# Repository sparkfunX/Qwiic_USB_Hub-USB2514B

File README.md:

SparkFun USB251xB Arduino Library
========================================

[*SparkX USB Hub - USB2514B (Qwiic) (SPX-18014)*](https://www.sparkfun.com/products/18014)

The USB2514 is a 4-port 2.0 USB hub. Who cares about USB 2.0 these days? The vast majority of projects we work on have a simple USB-to-Serial IC on it that do not require gigabit datarates. The USB251xB is a simple hub IC allowing multiple USB things to live under one USB connection; this is especially useful when prototyping a new product where you want the user to plug in just one cable.

The USB2514X is 4 port, the USB2513X is 3 port, and the USB2512X is 2 port. This library should work with all USB251xB ICs and may work with USB251x (non-B) variant ICs.

SparkFun labored with love to create this code. Feel like supporting open source hardware? 
Buy a [board](https://www.sparkfun.com/products/18014) from SparkFun!

Repository Contents
-------------------

* **/examples** - Example code to be used in the Arduino IDE.
* **/src** - Source files for the library (.cpp, .h).
* **keywords.txt** - Keywords from this library that will be highlighted in the Arduino IDE.
* **libaray.properties** - General library properties for the Arduino package manager

Documentation
--------------

* **[Installing an Arduino Library Guide](https://learn.sparkfun.com/tutorials/installing-an-arduino-library)** - Basic information on how to install an Arduino library.
* **[Product Repository](https://github.com/sparkfun/SparkFun_High_Precision_Temperature_Sensor_TMP117_Qwiic)** - Main repository (including hardware files)

Products that use this Repository
--------------

* [SPX-18014](https://www.sparkfun.com/products/18014)

License Information
-------------------

This product is _**open source**_! 

Please review the LICENSE.md file for license information. 

If you have any questions or concerns on licensing, please contact technical support on our [SparkFun forums](https://forum.sparkfun.com/viewforum.php?f=152).

Distributed as-is; no warranty is given.

- Your friends at SparkFun.

_<COLLABORATION CREDIT>_

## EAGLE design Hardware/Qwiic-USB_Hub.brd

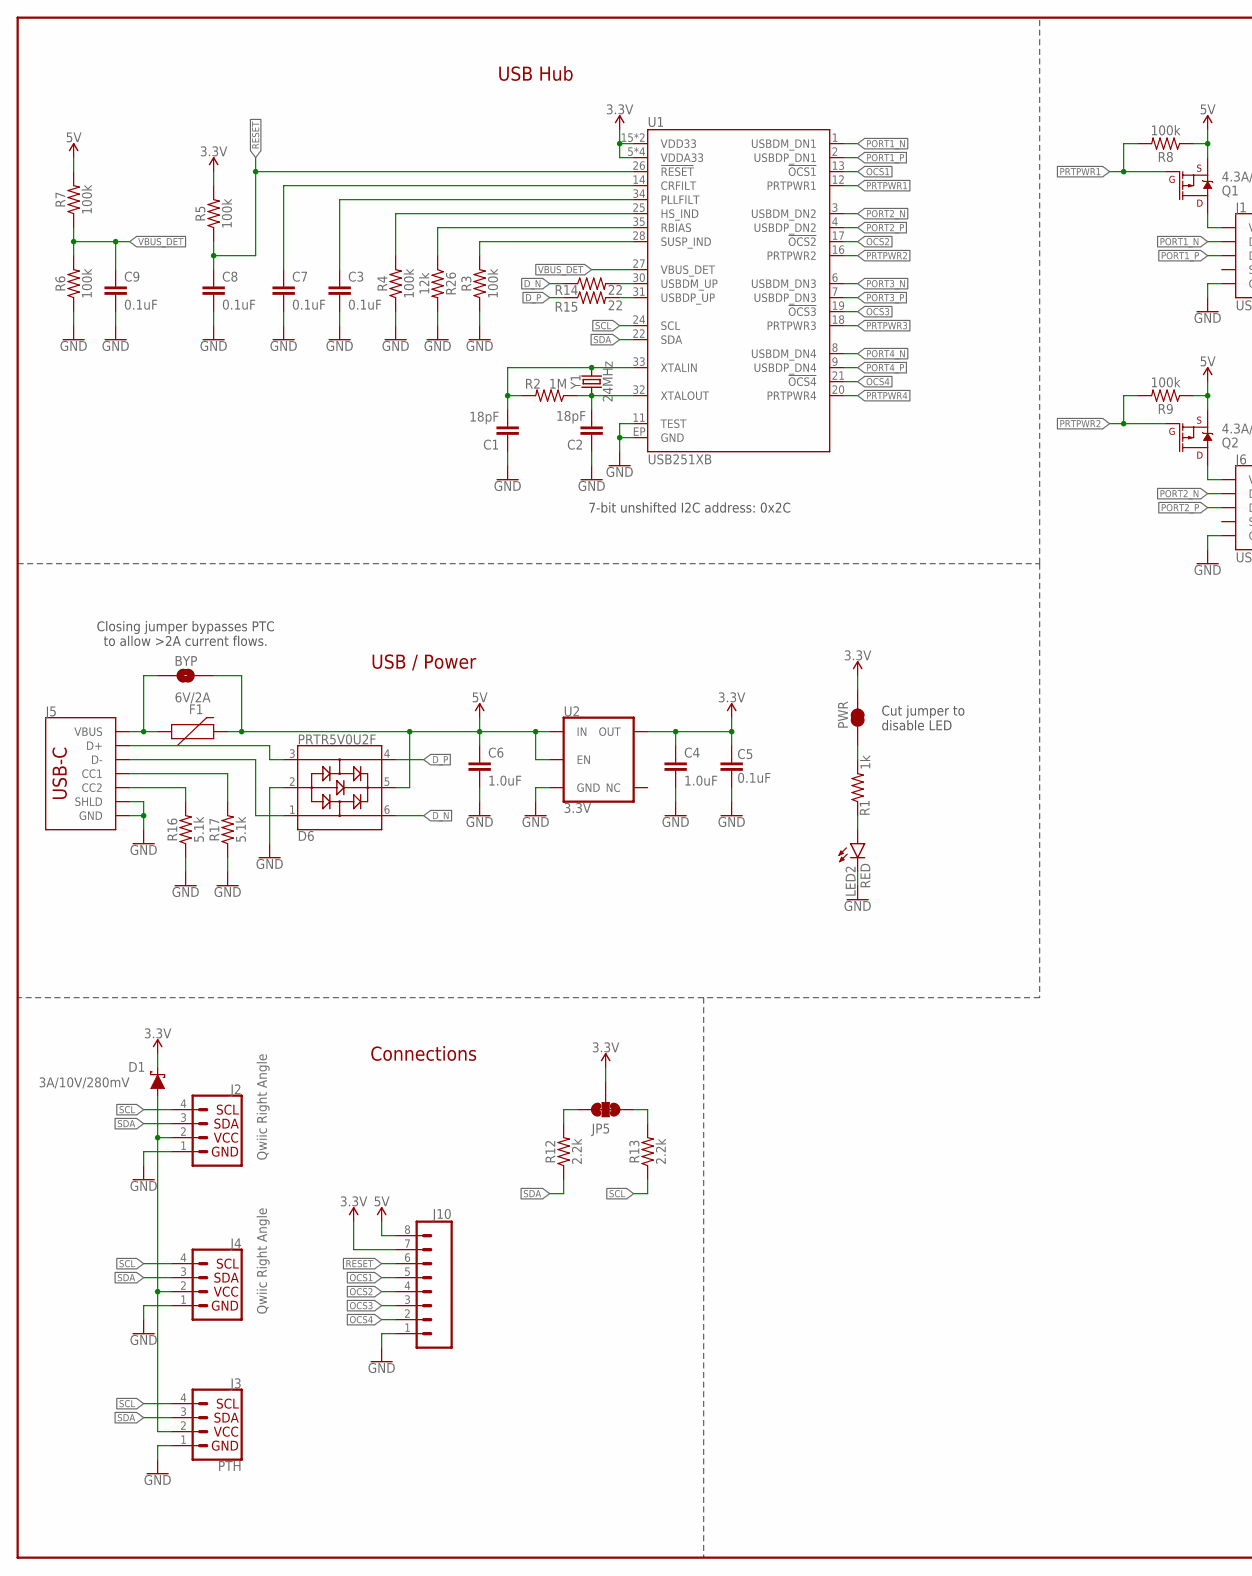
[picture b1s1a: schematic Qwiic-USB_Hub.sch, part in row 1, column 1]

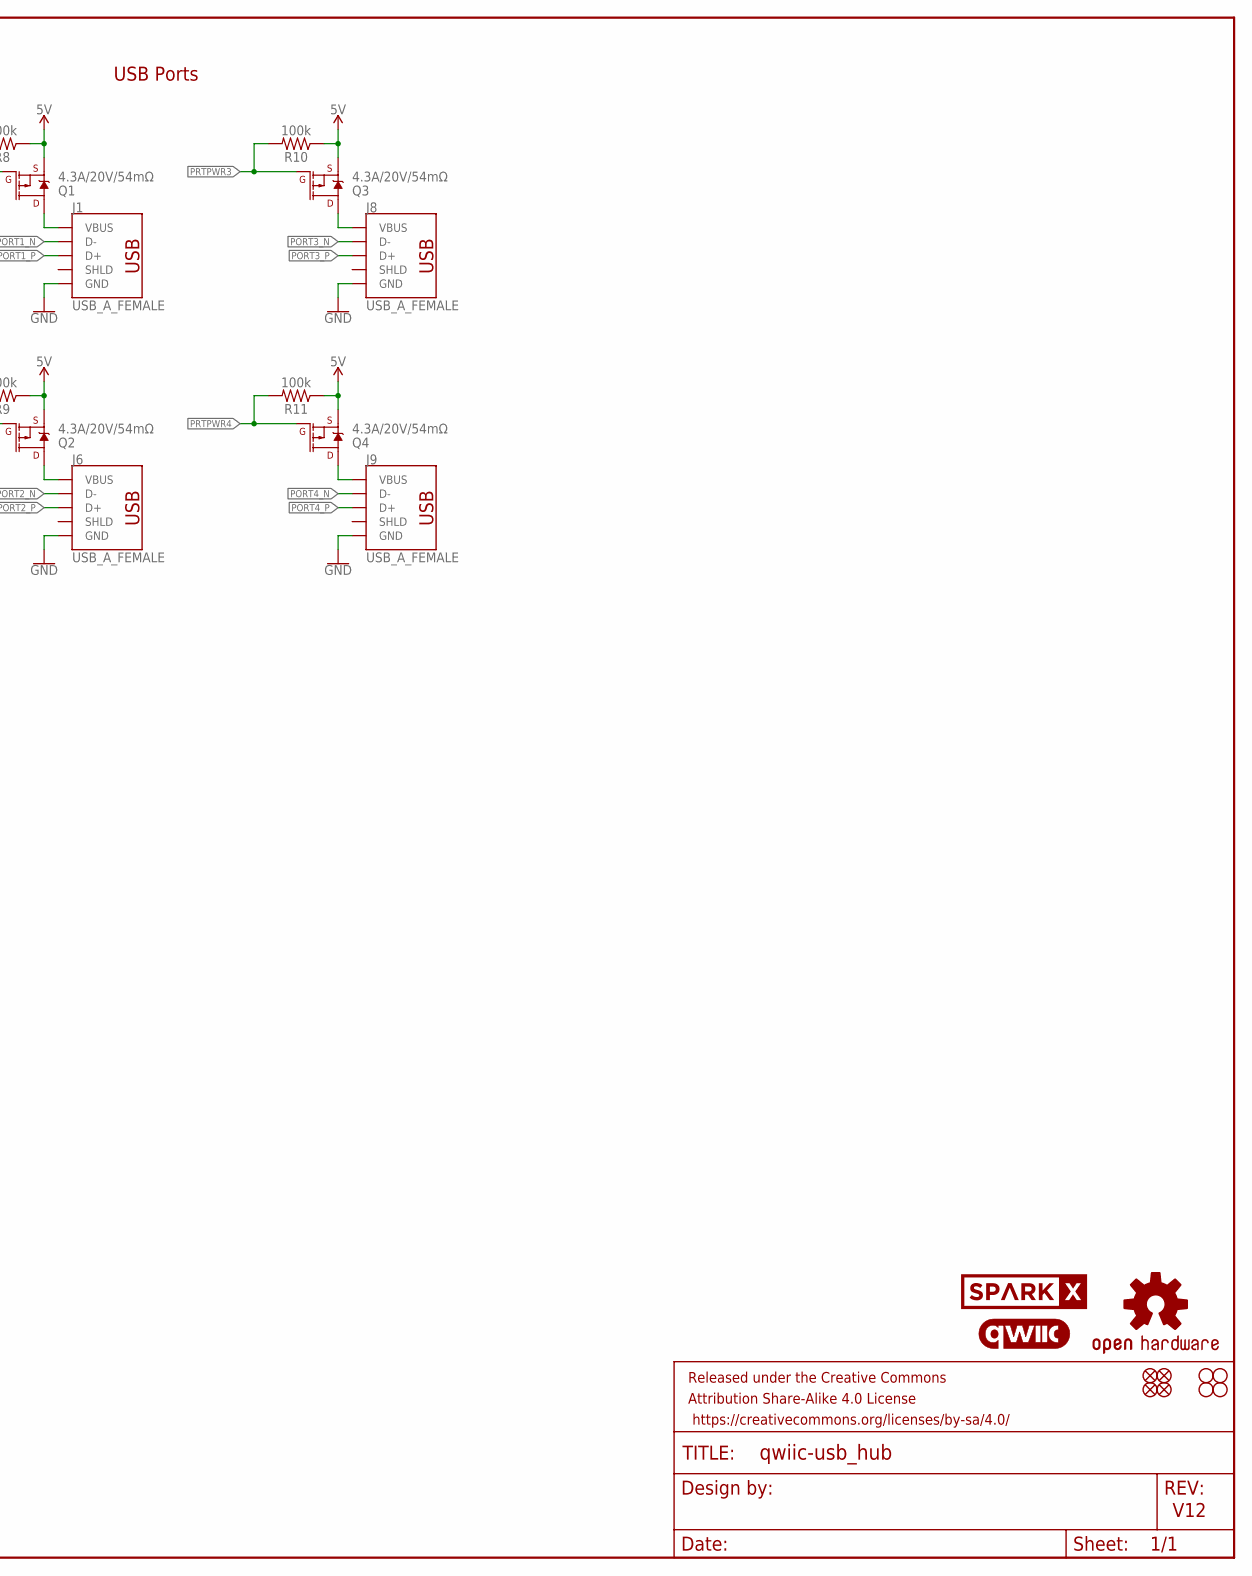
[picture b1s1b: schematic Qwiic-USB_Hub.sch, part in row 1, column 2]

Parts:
BYP: JUMPER-SMT_2_NO_SILK; SMT-JUMPER_2_NO_SILK
C1, C2: 18pF; 0603
C3, C5, C7, C8, C9: 0.1uF; 0603
C4, C6: 1.0uF; 0603
D1: 3A/10V/280mV; SOD-323
D6: PRTR5V0U2F; SOT886
F1: 6V/2A; 1210
FRAME2: FRAME-LEDGER; CREATIVE_COMMONS
J1, J6, J8, J9: USB_A_FEMALE; USB-A-S-NOSILK-FEMALE
J2, J4: Qwiic Right Angle; JST04_1MM_RA
J3: PTH; 1X04_NO_SILK
J5: USB_C_2-LAYER_PADS; USB-C-16P-2LAYER-PADS
J10: CONN_08NO_SILK_FEMALE_PTH; 1X08_NO_SILK
JP5: JUMPER-SMT_3_2-NC_TRACE_SILK; SMT-JUMPER_3_2-NC_TRACE_SILK
JP21, JP61, JP71, JP81: FIDUCIALUFIDUCIAL; MICRO-FIDUCIAL
JP31, JP41, JP91, JP101: STAND-OFF
LED2: RED; LED-0603
LOGO1: OSHW-LOGOMINI; OSHW-LOGO-MINI
LOGO2: QWIIC_LOGO_CONNECTOR; QWIIC_5.5MM
PWR: JUMPER-SMT_2_NC_TRACE_SILK; SMT-JUMPER_2_NC_TRACE_SILK
Q1, Q2, Q3, Q4: 4.3A/20V/54mΩ; SOT23-3
R1: 1k; 0603
R2: 1M; 0603
R3, R4, R5, R6, R7, R8, R9, R10, R11: 100k; 0603
R12, R13: 2.2k; 0603
R14, R15: 22; 0603
R16, R17: 5.1k; 0603
R26: 12k; 0603
U1: USB251XB; QFN-36
U2: 3.3V; SOT23-5
U$5: SPARKX-LOGO4; SPARKX-MEDIUM
Y1: 24MHz; CRYSTAL-SMD-2.0X1.6MM

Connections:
3.3V: C4.1, C5.2, D1.C, J10.7, JP5.2, PWR.2, R5.2, U1.5 (VDDA33), U1.10 (VDDA33), U1.15 (VDD33), U1.23 (VDD33), U1.29 (VDDA33), U1.36 (VDDA33), U2.5 (OUT)
5V: BYP.2, C6.1, D6.5, F1.2, J10.8, Q1.2 (S), Q2.2 (S), Q3.2 (S), Q4.2 (S), R7.2, R8.1, R9.1, R10.1, R11.1, U2.1 (IN), U2.3 (EN)
!OCS1: J10.5, U1.13 (!OCS1)
!OCS2: J10.4, U1.17 (!OCS2)
!OCS3: J10.3, U1.19 (!OCS3)
!OCS4: J10.2, U1.21 (!OCS4)
!RESET: C8.1, J10.6, R5.1, U1.26 (!RESET)
CC1: J5.A5 (CC1), R17.2
CC2: J5.B5 (CC2), R16.2
D_N: D6.6, R14.1
D_P: D6.4, R15.1
GND: C1.1, C2.1, C3.2, C4.2, C5.1, C6.2, C7.2, C8.2, C9.2, D6.2, J1.GND, J2.1, J3.1 (GND), J4.1, J5.GND, J5.GND2 (GND), J5.SHLD1 (SHLD), J5.SHLD2 (SHLD), J5.SHLD3 (SHLD), J5.SHLD4 (SHLD), J6.GND, J8.GND, J9.GND, J10.1, LED2.C, R3.1, R4.1, R6.1, R16.1, R17.1, R26.2, U1.11 (TEST), U1.EP (GND), U2.2 (GND)
unnamed: J1.VBUS, Q1.3 (D)
unnamed: J6.VBUS, Q2.3 (D)
unnamed: J8.VBUS, Q3.3 (D)
unnamed: J9.VBUS, Q4.3 (D)
unnamed: R26.1, U1.35 (RBIAS)
unnamed: C1.2, R2.2, U1.33 (XTALIN), Y1.3 (2)
unnamed: BYP.1, F1.1, J5.VBUS1 (VBUS), J5.VBUS2 (VBUS)
unnamed: C2.2, R2.1, U1.32 (XTALOUT), Y1.1
unnamed: JP5.1, R13.2
unnamed: LED2.A, R1.1
unnamed: R3.2, U1.28 (SUSP_IND)
unnamed: R4.2, U1.25 (HS_IND)
unnamed: C3.1, U1.34 (PLLFILT)
unnamed: C7.1, U1.14 (CRFILT)
unnamed: JP5.3, R12.2
unnamed: R14.2, U1.30 (USBDM_UP)
unnamed: PWR.1, R1.2
unnamed: R15.2, U1.31 (USBDP_UP)
unnamed: D1.A, J2.2, J3.2 (VCC), J4.2
PORT1_N: J1.D-, U1.1 (USBDM_DN1)
PORT1_P: J1.D+, U1.2 (USBDP_DN1)
PORT2_N: J6.D-, U1.3 (USBDM_DN2)
PORT2_P: J6.D+, U1.4 (USBDP_DN2)
PORT3_N: J8.D-, U1.6 (USBDM_DN3)
PORT3_P: J8.D+, U1.7 (USBDP_DN3)
PORT4_N: J9.D-, U1.8 (USBDM_DN4)
PORT4_P: J9.D+, U1.9 (USBDP_DN4)
PRTPWR1: Q1.1 (G), R8.2, U1.12 (PRTPWR1)
PRTPWR2: Q2.1 (G), R9.2, U1.16 (PRTPWR2)
PRTPWR3: Q3.1 (G), R10.2, U1.18 (PRTPWR3)
PRTPWR4: Q4.1 (G), R11.2, U1.20 (PRTPWR4)
SCL: J2.4, J3.4 (SCL), J4.4, R13.1, U1.24 (SCL)
SDA: J2.3, J3.3 (SDA), J4.3, R12.1, U1.22 (SDA)
UNP_D+: D6.3, J5.A6 (D+), J5.B6 (D+)
UNP_D-: D6.1, J5.A7 (D-), J5.B7 (D-)
VBUS_DET: C9.1, R6.2, R7.1, U1.27 (VBUS_DET)

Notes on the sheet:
V12
7-bit unshifted I2C address: 0x2C
Cut jumper to disable LED
USB Hub
USB / Power
USB Ports
Connections
Closing jumper bypasses PTC to allow >2A current flows.

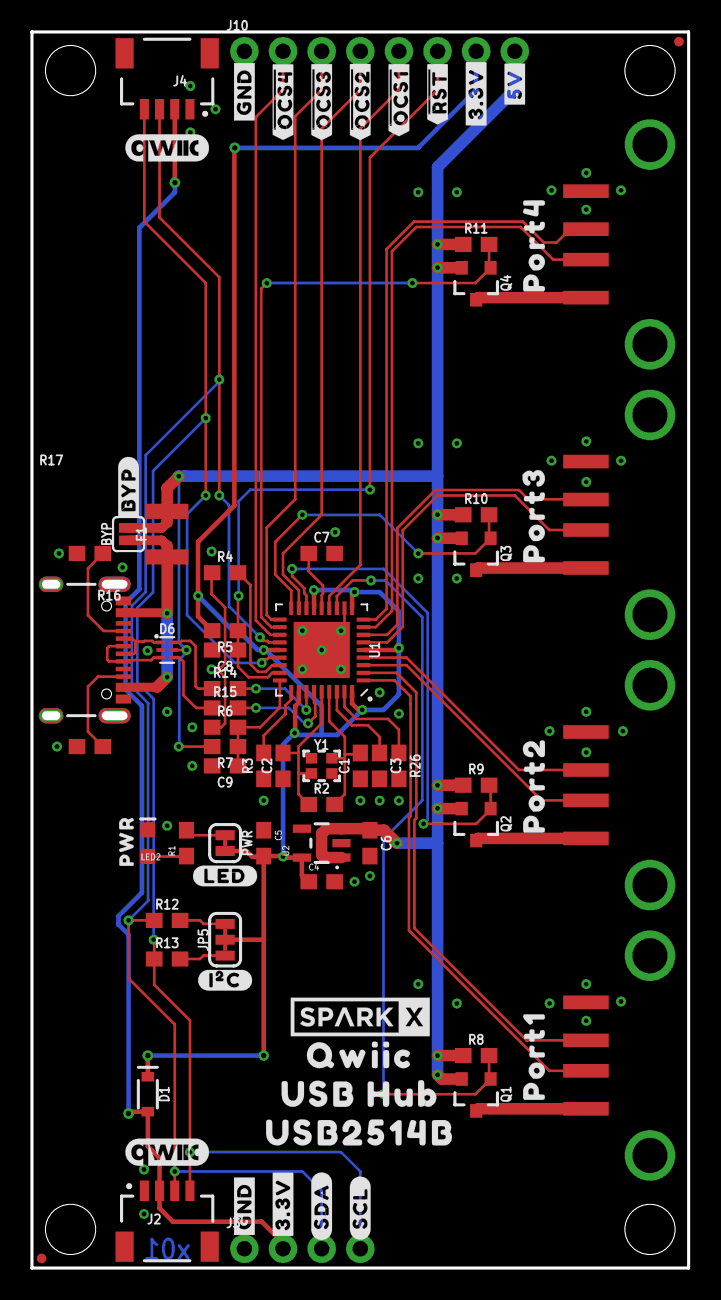
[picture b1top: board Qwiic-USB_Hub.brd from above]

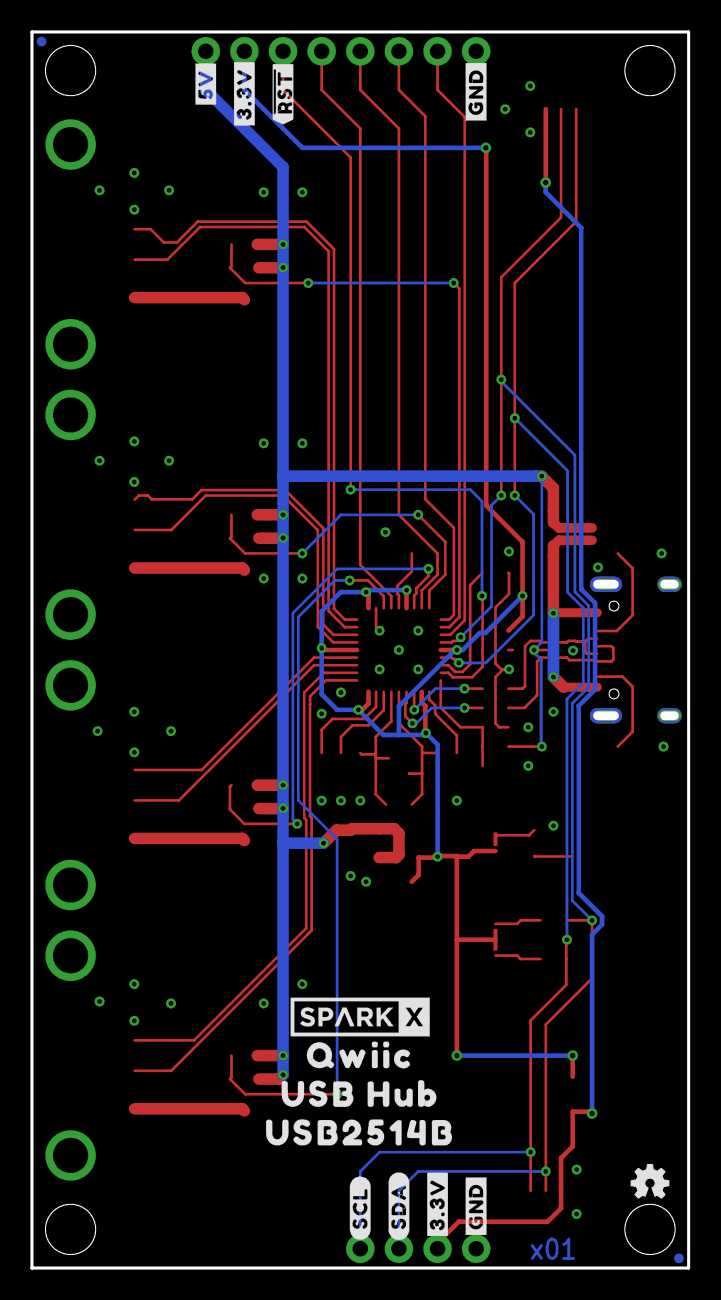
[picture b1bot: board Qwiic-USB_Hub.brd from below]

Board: 2 copper layers, 42.8 x 80.9 mm, 98 parts (15 on the bottom side), 48 nets.

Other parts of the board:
U$1: PORT40
U$2: PORT31
U$3: PORT22
U$4: PORT13
U$6, U$34: #3#3V#0
U$7, U$35: #SDA#0
U$8, U$36: #SCL#0
U$9, U$33: #GND#0
U$10: #I�C#1
U$11, U$16: #GND#5
U$12: PWR0
U$13, U$31: ##RST##4
U$14, U$32: #3#3V#6
U$15, U$37: #5V#7
U$17: ##OCS1##3
U$18: ##OCS2##2
U$19: ##OCS3##1
U$20: ##OCS4##0
U$21: #BYP#0
U$22, U$39: QWIIC2
U$23: #LED#0
U$26, U$41: USB2514B0
U$27, U$40: USB_HUB1
U$38: SPARKX-LOGO4; SPARKX-MEDIUM
U$42: QWIIC_5.5MM

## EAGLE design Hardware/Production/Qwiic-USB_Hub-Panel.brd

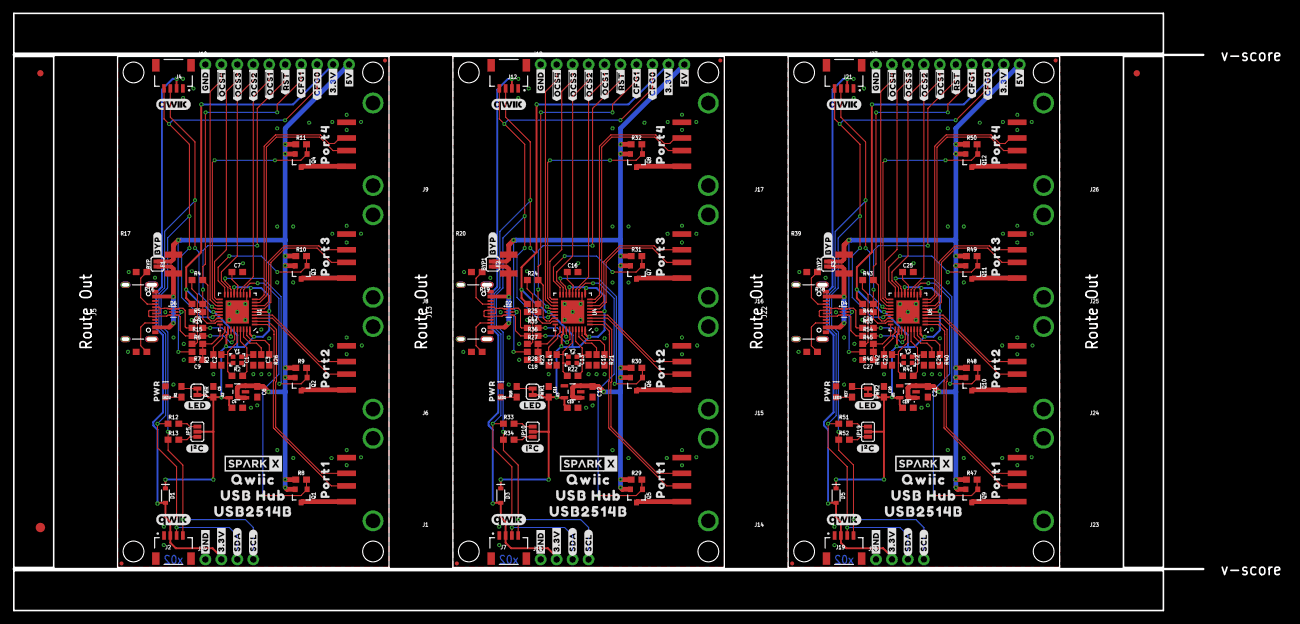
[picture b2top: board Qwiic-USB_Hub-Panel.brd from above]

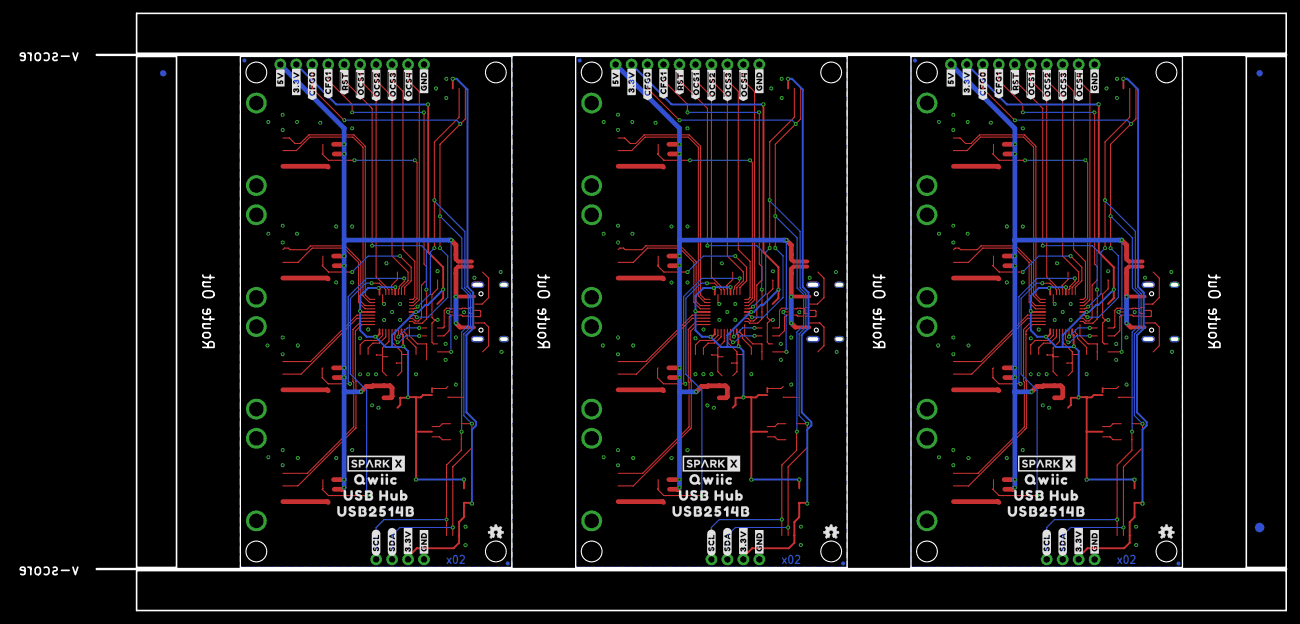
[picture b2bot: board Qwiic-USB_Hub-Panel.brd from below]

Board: 2 copper layers, 202.2 x 94.7 mm, 321 parts (66 on the bottom side), 144 nets.

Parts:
BYP, BYP1, BYP2: JUMPER-SMT_2_NO_SILK; SMT-JUMPER_2_NO_SILK
C1, C2, C13, C14, C22, C23: 18pF; 0603
C3, C5, C7, C8, C9, C11, C15, C16, C17, C18, C20, C24, C25, C26, C27: 0.1uF; 0603
C4, C6, C10, C12, C19, C21: 1.0uF; 0603
D1, D3, D5: 3A/10V/280mV; SOD-323
D2, D4, D6: PRTR5V0U2F; SOT886
E$1, E$2, E$3, E$4: FIDUCIAL-1X2
E$5, E$6: FIDUCIAL-1.5X3
F1, F2, F3: 6V/2A; 1210
J1, J6, J8, J9, J14, J15, J16, J17, J23, J24, J25, J26: USB_A_FEMALE; USB-A-S-NOSILK-FEMALE
J2, J4, J7, J12, J19, J21: Qwiic Right Angle; JST04_1MM_RA
J3, J11, J20: PTH; 1X04_NO_SILK
J5, J13, J22: USB-C-16P-2LAYER-PADS
J10, J18, J27: 1X10_NO_SILK
JP1, JP2, JP8, JP9, JP11, JP12, JP17, JP18, JP31, JP41, JP91, JP101: STAND-OFF
JP3, JP4, JP6, JP7, JP13, JP14, JP15, JP16, JP21, JP61, JP71, JP81: FIDUCIALUFIDUCIAL; MICRO-FIDUCIAL
JP5, JP10, JP19: SMT-JUMPER_3_NO_SILK
LED1, LED2, LED3: RED; LED-0603
LOGO1, LOGO3, LOGO5: OSHW-LOGOMINI; OSHW-LOGO-MINI
LOGO2, LOGO4, LOGO6: QWIIC_LOGO_CONNECTOR; QWIIC_5.5MM
PWR, PWR1, PWR2: SMT-JUMPER_2_NC_TRACE_SILK
Q1, Q2, Q3, Q4, Q5, Q6, Q7, Q8, Q9, Q10, Q11, Q12: 4.3A/20V/54mΩ; SOT23-3
R1, R18, R37: 1k; 0603
R2, R22, R41: 1M; 0603
R3, R4, R5, R6, R7, R8, R9, R10, R11, R23, R24, R25, R27, R28, R29, R30, R31, R32, R42, R43, R44, R45, R46, R47, R48, R49, R50: 100k; 0603
R12, R13, R33, R34, R51, R52: 2.2k; 0603
R14, R15, R35, R36, R53, R54: 22; 0603
R16, R17, R19, R20, R38, R39: 5.1k; 0603
R21, R26, R40: 12k; 0603
U1, U4, U6: USB251XB; QFN-36
U2, U3, U5: 3.3V; SOT23-5
U$1, U$46, U$91: PORT40
U$2, U$47, U$92: PORT31
U$3, U$48, U$93: PORT22
U$4, U$49, U$94: PORT13
U$5, U$38, U$50, U$74, U$95, U$119: SPARKX-LOGO4; SPARKX-MEDIUM
U$6, U$34, U$51, U$54, U$96, U$99: #3#3V#0
U$7, U$35, U$52, U$55, U$97, U$100: #SDA#0
U$8, U$36, U$53, U$56, U$98, U$101: #SCL#0
U$9, U$33, U$57, U$58, U$102, U$103: #GND#0
U$10, U$59, U$104: #I�C#1
U$11, U$16, U$64, U$70, U$109, U$115: #GND#5
U$12, U$60, U$105: PWR0
U$13, U$31, U$61, U$71, U$106, U$116: ##RST##4
U$14, U$32, U$62, U$72, U$107, U$117: #3#3V#6
U$15, U$37, U$63, U$73, U$108, U$118: #5V#7
U$17, U$30, U$79, U$87, U$124, U$132: ##OCS1##3
U$18, U$43, U$80, U$88, U$125, U$133: ##OCS2##2
U$19, U$44, U$81, U$89, U$126, U$134: ##OCS3##1
U$20, U$45, U$82, U$90, U$127, U$135: ##OCS4##0
U$21, U$65, U$110: #BYP#0
U$22, U$39, U$67, U$75, U$112, U$120: QWIIC2
U$23, U$69, U$114: #LED#0
U$24, U$29, U$83, U$86, U$128, U$131: #CFG0#1
U$25, U$28, U$84, U$85, U$129, U$130: #CFG1#0
U$26, U$41, U$66, U$77, U$111, U$122: USB2514B0
U$27, U$40, U$68, U$76, U$113, U$121: USB_HUB1
U$42, U$78, U$123: QWIIC_5.5MM
Y1, Y2, Y3: 24MHz; CRYSTAL-SMD-2.0X1.6MM

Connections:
3.3V: C4.1, C5.2, D1.C, J10.9, JP5.2, PWR.2, R5.2, U1.5, U1.10, U1.15, U1.23, U1.29, U1.36, U2.5
3.3V1: C10.1, C11.2, D3.C, J18.9, JP10.2, PWR1.2, R25.2, U3.5, U4.5, U4.10, U4.15, U4.23, U4.29, U4.36
3.3V2: C19.1, C20.2, D5.C, J27.9, JP19.2, PWR2.2, R44.2, U5.5, U6.5, U6.10, U6.15, U6.23, U6.29, U6.36
5V: BYP.2, C6.1, D6.5, F1.2, J10.10, Q1.2, Q2.2, Q3.2, Q4.2, R7.2, R8.1, R9.1, R10.1, R11.1, U2.1, U2.3
5V1: BYP1.2, C12.1, D2.5, F2.2, J18.10, Q5.2, Q6.2, Q7.2, Q8.2, R28.2, R29.1, R30.1, R31.1, R32.1, U3.1, U3.3
5V2: BYP2.2, C21.1, D4.5, F3.2, J27.10, Q9.2, Q10.2, Q11.2, Q12.2, R46.2, R47.1, R48.1, R49.1, R50.1, U5.1, U5.3
!OCS1: J10.5, U1.13
!OCS2: J10.4, U1.17
!OCS3: J10.3, U1.19
!OCS4: J10.2, U1.21
!OCS5: J18.5, U4.13
!OCS6: J18.4, U4.17
!OCS7: J18.3, U4.19
!OCS8: J18.2, U4.21
!OCS9: J27.5, U6.13
!OCS10: J27.4, U6.17
!OCS11: J27.3, U6.19
!OCS12: J27.2, U6.21
!RESET: C8.1, J10.6, R5.1, U1.26
!RESET1: C17.1, J18.6, R25.1, U4.26
!RESET2: C26.1, J27.6, R44.1, U6.26
CC1: J5.A5, R17.2
CC2: J5.B5, R16.2
CC3: J13.A5, R20.2
CC4: J13.B5, R19.2
CC5: J22.A5, R39.2
CC6: J22.B5, R38.2
CFG1: J10.7, R4.2, U1.25
CFG2: J18.7, R24.2, U4.25
CFG3: J27.7, R43.2, U6.25
D_N: D6.6, R14.1
D_N1: D2.6, R35.1
D_N2: D4.6, R53.1
D_P: D6.4, R15.1
D_P1: D2.4, R36.1
D_P2: D4.4, R54.1
GND: C1.1, C2.1, C3.2, C4.2, C5.1, C6.2, C7.2, C8.2, C9.2, D6.2, J1.GND, J2.1, J3.1, J4.1, J5.GND, J5.GND2, J5.SHLD1, J5.SHLD2, J5.SHLD3, J5.SHLD4, J6.GND, J8.GND, J9.GND, J10.1, LED2.C, R3.1, R4.1, R6.1, R16.1, R17.1, R26.2, U1.11, U1.EP, U2.2
GND1: C10.2, C11.1, C12.2, C13.1, C14.1, C15.2, C16.2, C17.2, C18.2, D2.2, J7.1, J11.1, J12.1, J13.GND, J13.GND2, J13.SHLD1, J13.SHLD2, J13.SHLD3, J13.SHLD4, J14.GND, J15.GND, J16.GND, J17.GND, J18.1, LED1.C, R19.1, R20.1, R21.2, R23.1, R24.1, R27.1, U3.2, U4.11, U4.EP
GND2: C19.2, C20.1, C21.2, C22.1, C23.1, C24.2, C25.2, C26.2, C27.2, D4.2, J19.1, J20.1, J21.1, J22.GND, J22.GND2, J22.SHLD1, J22.SHLD2, J22.SHLD3, J22.SHLD4, J23.GND, J24.GND, J25.GND, J26.GND, J27.1, LED3.C, R38.1, R39.1, R40.2, R42.1, R43.1, R45.1, U5.2, U6.11, U6.EP
unnamed: J1.VBUS, Q1.3
unnamed: J6.VBUS, Q2.3
unnamed: J8.VBUS, Q3.3
unnamed: J9.VBUS, Q4.3
unnamed: R26.1, U1.35
unnamed: C1.2, R2.2, U1.33, Y1.3
unnamed: BYP.1, F1.1, J5.VBUS1, J5.VBUS2
unnamed: C2.2, R2.1, U1.32, Y1.1
unnamed: JP5.1, R13.2
unnamed: LED2.A, R1.1
unnamed: R3.2, U1.28
unnamed: LED1.A, R18.1
unnamed: C3.1, U1.34
unnamed: C7.1, U1.14
unnamed: JP5.3, R12.2
unnamed: R14.2, U1.30
unnamed: PWR.1, R1.2
unnamed: R15.2, U1.31
unnamed: PWR1.1, R18.2
unnamed: C13.2, R22.2, U4.33, Y2.3
unnamed: D1.A, J2.2, J3.2, J4.2
unnamed: C14.2, R22.1, U4.32, Y2.1
unnamed: R21.1, U4.35
unnamed: R23.2, U4.28
unnamed: C15.1, U4.34
unnamed: C16.1, U4.14
unnamed: J14.VBUS, Q5.3
unnamed: J15.VBUS, Q6.3
unnamed: J16.VBUS, Q7.3
unnamed: J17.VBUS, Q8.3
unnamed: BYP1.1, F2.1, J13.VBUS1, J13.VBUS2
unnamed: JP10.1, R34.2
unnamed: JP10.3, R33.2
unnamed: R35.2, U4.30
unnamed: R36.2, U4.31
unnamed: D3.A, J7.2, J11.2, J12.2
unnamed: LED3.A, R37.1
unnamed: PWR2.1, R37.2
unnamed: C22.2, R41.2, U6.33, Y3.3
unnamed: C23.2, R41.1, U6.32, Y3.1
unnamed: R40.1, U6.35
unnamed: R42.2, U6.28
unnamed: C24.1, U6.34
unnamed: C25.1, U6.14
unnamed: J23.VBUS, Q9.3
unnamed: J24.VBUS, Q10.3
unnamed: J25.VBUS, Q11.3
unnamed: J26.VBUS, Q12.3
unnamed: BYP2.1, F3.1, J22.VBUS1, J22.VBUS2
unnamed: JP19.1, R52.2
unnamed: JP19.3, R51.2
unnamed: R53.2, U6.30
unnamed: R54.2, U6.31
unnamed: D5.A, J19.2, J20.2, J21.2
PORT1_N: J1.D-, U1.1
PORT1_N1: J14.D-, U4.1
PORT1_N2: J23.D-, U6.1
PORT1_P: J1.D+, U1.2
PORT1_P1: J14.D+, U4.2
PORT1_P2: J23.D+, U6.2
PORT2_N: J6.D-, U1.3
PORT2_N1: J15.D-, U4.3
PORT2_N2: J24.D-, U6.3
PORT2_P: J6.D+, U1.4
PORT2_P1: J15.D+, U4.4
PORT2_P2: J24.D+, U6.4
PORT3_N: J8.D-, U1.6
PORT3_N1: J16.D-, U4.6
PORT3_N2: J25.D-, U6.6
PORT3_P: J8.D+, U1.7
PORT3_P1: J16.D+, U4.7
PORT3_P2: J25.D+, U6.7
PORT4_N: J9.D-, U1.8
PORT4_N1: J17.D-, U4.8
PORT4_N2: J26.D-, U6.8
PORT4_P: J9.D+, U1.9
PORT4_P1: J17.D+, U4.9
PORT4_P2: J26.D+, U6.9
PRTPWR1: Q1.1, R8.2, U1.12
PRTPWR2: Q2.1, R9.2, U1.16
PRTPWR3: Q3.1, R10.2, U1.18
PRTPWR4: Q4.1, R11.2, U1.20
PRTPWR5: Q5.1, R29.2, U4.12
PRTPWR6: Q6.1, R30.2, U4.16
PRTPWR7: Q7.1, R31.2, U4.18
PRTPWR8: Q8.1, R32.2, U4.20
PRTPWR9: Q9.1, R47.2, U6.12
PRTPWR10: Q10.1, R48.2, U6.16
PRTPWR11: Q11.1, R49.2, U6.18
PRTPWR12: Q12.1, R50.2, U6.20
SCL/CFG0: J2.4, J3.4, J4.4, J10.8, R13.1, U1.24
SCL/CFG1: J7.4, J11.4, J12.4, J18.8, R34.1, U4.24
SCL/CFG2: J19.4, J20.4, J21.4, J27.8, R52.1, U6.24
SDA: J2.3, J3.3, J4.3, R12.1, U1.22
SDA1: J7.3, J11.3, J12.3, R33.1, U4.22
SDA2: J19.3, J20.3, J21.3, R51.1, U6.22
UNP_D+: D6.3, J5.A6, J5.B6
UNP_D+1: D2.3, J13.A6, J13.B6
UNP_D+2: D4.3, J22.A6, J22.B6
UNP_D-: D6.1, J5.A7, J5.B7
UNP_D-1: D2.1, J13.A7, J13.B7
UNP_D-2: D4.1, J22.A7, J22.B7
VBUS_DET: C9.1, R6.2, R7.1, U1.27
VBUS_DET1: C18.1, R27.2, R28.1, U4.27
VBUS_DET2: C27.1, R45.2, R46.1, U6.27

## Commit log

2021-02-04 Remove old files
2021-02-04 Add ignore. Increase 3.3V width.
2021-02-04 Add labels to bottom layer.
2021-02-05 Fixing silk typo in OCS labels. Adding production panels.
2021-02-22 Add Prod ID
2021-04-17 Add connections to config pins.
2021-04-17 Panel for x02
2021-04-17 Increase x02 panel size.
2021-06-09 Add schematic and readme.

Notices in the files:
parts and their libraries:
SparkFun-Resistors: Licensing: Creative Commons ShareAlike 4.0 International - https://creativecommons.org/licenses/by-sa/4.0
SparkFun-Aesthetics: Released under the Creative Commons Attribution Share-Alike 4.0 License
SparkFun-Aesthetics: https://creativecommons.org/licenses/by-sa/4.0
